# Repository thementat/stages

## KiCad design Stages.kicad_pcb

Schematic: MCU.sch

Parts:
C3, C4: 20p; C_0805_2012Metric
C9: 22u; C_1206_3216Metric
C11, C13, C14, C24: 100n; C_0805_2012Metric
C12, C26: 1u; C_0805_2012Metric
IC5: STM32F373RBTx; LQFP-64_10x10mm_P0.5mm
JP3, JP4: Conn_01x03; PinHeader_1x03_P2.54mm_Vertical
JP6: Conn_01x04; PinHeader_1x04_P2.54mm_Vertical
Q1: 8MHz; Crystal_SMD_Abracon_ABMM2-4Pin_6.0x3.6mm_HandSoldering
R5, R7, R8, R9, R10, R11: 100; R_0805_2012Metric
R12: 10k; R_0805_2012Metric

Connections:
+3V3: C9.1, C11.1, C14.1, IC5.1 (VBAT), IC5.19 (VDD), IC5.64 (VDD), R12.2; also elsewhere on the board
+3V3_A: C12.1, C13.1, C24.1, C26.1, IC5.13 (VDDA), IC5.17 (VREF+), IC5.32 (VDDSD), IC5.33 (VREFSD+); also elsewhere on the board
ADC_CV_1: IC5.34 (PB14); also elsewhere on the board
ADC_CV_2: IC5.35 (PB15); also elsewhere on the board
ADC_CV_3: IC5.29 (PE8); also elsewhere on the board
ADC_CV_4: IC5.30 (PE9); also elsewhere on the board
ADC_CV_5: IC5.27 (PB1); also elsewhere on the board
ADC_CV_6: IC5.26 (PB0); also elsewhere on the board
ADC_SHAPE: IC5.22 (PA6); also elsewhere on the board
ADC_TIME_LEVEL: IC5.23 (PA7); also elsewhere on the board
DAC_MOSI: IC5.53 (PC12); also elsewhere on the board
DAC_SCK: IC5.51 (PC10); also elsewhere on the board
DAC_SS: IC5.50 (PA15); also elsewhere on the board
GATE_1: IC5.44 (PA11); also elsewhere on the board
GATE_2: IC5.43 (PA10); also elsewhere on the board
GATE_3: IC5.42 (PA9); also elsewhere on the board
GATE_4: IC5.41 (PA8); also elsewhere on the board
GATE_5: IC5.39 (PC8); also elsewhere on the board
GATE_6: IC5.38 (PC7); also elsewhere on the board
LEDS_SCK: IC5.58 (PB6); also elsewhere on the board
LEDS_SIN: IC5.57 (PB5); also elsewhere on the board
LEDS_SS: IC5.59 (PB7); also elsewhere on the board
LEFT_RX: IC5.62 (PB9), R7.1
LEFT_TX: IC5.61 (PB8), R5.1
NORMALIZATION_PROBE: IC5.40 (PC9); also elsewhere on the board
unnamed: C3.2, Q1.1, R9.1
unnamed: C4.2, Q1.3, R8.1
unnamed: IC5.5 (PF0), R9.2
unnamed: IC5.6 (PF1), R8.2
unnamed: JP3.2, R5.2
unnamed: JP3.3, R7.2
unnamed: JP4.2, R10.2
unnamed: JP4.3, R11.2
POTS_ADDR_A: IC5.21 (PA5); also elsewhere on the board
POTS_ADDR_B: IC5.20 (PA4); also elsewhere on the board
POTS_ADDR_C: IC5.18 (PA3); also elsewhere on the board
RESET: IC5.7 (NRST), JP6.4, R12.1
RIGHT_RX: IC5.25 (PC5), R10.1
RIGHT_TX: IC5.24 (PC4), R11.1
STAGE_LED_1: IC5.45 (PA12); also elsewhere on the board
STAGE_LED_2: IC5.2 (PC13); also elsewhere on the board
STAGE_LED_3: IC5.3 (PC14); also elsewhere on the board
STAGE_LED_4: IC5.4 (PC15); also elsewhere on the board
STAGE_LED_5: IC5.16 (PA2); also elsewhere on the board
STAGE_LED_6: IC5.28 (PB2); also elsewhere on the board
SWCLK: IC5.49 (PA14), JP6.3
SWDIO: IC5.46 (PA13), JP6.2
SW_MODE_1: IC5.8 (PC0); also elsewhere on the board
SW_MODE_2: IC5.9 (PC1); also elsewhere on the board
SW_MODE_3: IC5.10 (PC2); also elsewhere on the board
SW_MODE_4: IC5.11 (PC3); also elsewhere on the board
SW_MODE_5: IC5.14 (PA0); also elsewhere on the board
SW_MODE_6: IC5.15 (PA1); also elsewhere on the board

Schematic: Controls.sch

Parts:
C5, C7, C8, C16: 100n; C_0805_2012Metric
C6: 22u; C_1206_3216Metric
IC1: TLC59281; TSSOP-24_4.4x7.8mm_P0.65mm
IC3, IC6: 4051; TSSOP-16_4.4x5mm_P0.65mm
L2: Ferrite_Bead_Small; R_0805_2012Metric
LED7, LED8, LED9, LED10, LED11, LED12: LED_Dual_CAC; LED_3.0mm Bi-Color Common Anode
MH1, MH2, MH3: MountingHole; MountingHole_3.2mm_M3
R1, R2, R3, R4, R17, R18: 15k; R_0805_2012Metric
R6: 10k; R_0805_2012Metric
R78, R79, R80, R81, R82, R83: 20kB; Potentiometer-Bourns PTL20
R84, R85, R86, R87, R88, R89: 10kB; Potentiometer_SongHuei9mm-1_Single_Vertical
SW1, SW2, SW3, SW4, SW5, SW6: SW_Push_4pin; Push E-Switch 6mm

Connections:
+3V3: L2.1, LED7.2, LED8.2, LED9.2, LED10.2, LED11.2, LED12.2; also elsewhere on the board
+3V3_A: C5.1, C7.1, C16.1, IC3.16, IC6.16, R78.3, R79.3, R80.3, R81.3, R82.3, R83.3, R84.1, R85.1, R86.1, R87.1, R88.1, R89.1; also elsewhere on the board
ADC_SHAPE: IC3.3; also elsewhere on the board
ADC_TIME_LEVEL: IC6.3; also elsewhere on the board
LEDS_SCK: IC1.3; also elsewhere on the board
LEDS_SIN: IC1.2; also elsewhere on the board
LEDS_SS: IC1.4; also elsewhere on the board
unnamed: C6.1, C8.1, IC1.24, L2.2
unnamed: IC1.7, LED9.3
unnamed: IC1.8, LED9.1
unnamed: IC1.9, LED7.1
unnamed: IC1.10, LED7.3
unnamed: IC1.11, LED8.1
unnamed: IC1.12, LED8.3
unnamed: IC1.13, LED10.1
unnamed: IC1.14, LED10.3
unnamed: IC1.15, LED11.3
unnamed: IC1.16, LED11.1
unnamed: IC1.17, LED12.3
unnamed: IC1.18, LED12.1
unnamed: IC1.23, R6.1
unnamed: IC3.1, R86.2
unnamed: IC3.2, R85.2
unnamed: IC3.4, R89.2
unnamed: IC3.5, R84.2
unnamed: IC3.14, R87.2
unnamed: IC3.15, R88.2
unnamed: IC6.1, R78.2
unnamed: IC6.2, R83.2
unnamed: IC6.12, R82.2
unnamed: IC6.13, R81.2
unnamed: IC6.14, R80.2
unnamed: IC6.15, R79.2
unnamed: R1.1, R80.5
unnamed: R2.1, R81.5
unnamed: R3.1, R79.5
unnamed: R4.1, R82.5
unnamed: R17.1, R78.5
unnamed: R18.1, R83.5
POTS_ADDR_A: IC3.9, IC6.11; also elsewhere on the board
POTS_ADDR_B: IC3.10, IC6.10; also elsewhere on the board
POTS_ADDR_C: IC3.11, IC6.9; also elsewhere on the board
STAGE_LED_1: R17.2; also elsewhere on the board
STAGE_LED_2: R3.2; also elsewhere on the board
STAGE_LED_3: R1.2; also elsewhere on the board
STAGE_LED_4: R2.2; also elsewhere on the board
STAGE_LED_5: R4.2; also elsewhere on the board
STAGE_LED_6: R18.2; also elsewhere on the board
SW_MODE_1: SW1.3, SW1.4; also elsewhere on the board
SW_MODE_2: SW2.3, SW2.4; also elsewhere on the board
SW_MODE_3: SW3.3, SW3.4; also elsewhere on the board
SW_MODE_4: SW4.3, SW4.4; also elsewhere on the board
SW_MODE_5: SW5.3, SW5.4; also elsewhere on the board
SW_MODE_6: SW6.3, SW6.4; also elsewhere on the board

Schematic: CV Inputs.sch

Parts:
C27, C29, C31, C32, C35: 2.2n; C_0805_2012Metric
C28: 470p; C_0805_2012Metric
C30, C33, C34: 100n; C_0805_2012Metric
C36, C37, C38, C39, C40, C42: ESD; C_0805_2012Metric
IC8, IC9, IC10: MCP6002; SOIC-8_3.9x4.9mm_P1.27mm
J13, J14, J15, J16, J17, J18: -81V to 8.1V; WQP-PJ301M-12_JACK
R13, R14, R15, R16, R19, R20: 20k; R_0805_2012Metric
R21, R22, R23, R24, R26, R29: 30k; R_0805_2012Metric
R25, R27, R28, R30, R31, R32: 100k; R_0805_2012Metric

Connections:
+3V3_A: C30.1, C33.1, C34.1, IC8.8 (V+), IC9.8 (V+), IC10.8 (V+); also elsewhere on the board
ADC_CV_1: C35.1, IC10.7, R16.1; also elsewhere on the board
ADC_CV_2: C32.1, IC10.1, R14.1; also elsewhere on the board
ADC_CV_3: C31.1, IC9.7, R13.1; also elsewhere on the board
ADC_CV_4: C29.1, IC9.1, R15.1; also elsewhere on the board
ADC_CV_5: C27.1, IC8.7, R19.1; also elsewhere on the board
ADC_CV_6: C28.1, IC8.1, R20.1; also elsewhere on the board
AREF_-2.5: R21.2, R22.2, R23.2, R24.2, R26.2, R29.2; also elsewhere on the board
unnamed: C27.2, IC8.6 (-), R19.2, R24.1, R31.1
unnamed: C28.2, IC8.2 (-), R20.2, R23.1, R32.1
unnamed: C29.2, IC9.2 (-), R15.2, R22.1, R25.1
unnamed: C31.2, IC9.6 (-), R13.2, R26.1, R27.1
unnamed: C32.2, IC10.2 (-), R14.2, R21.1, R28.1
unnamed: C35.2, IC10.6 (-), R16.2, R29.1, R30.1
unnamed: C36.1, J17.P$1, R31.2
unnamed: C37.1, J15.P$1, R27.2
unnamed: C38.1, J13.P$1, R30.2
unnamed: C39.1, J14.P$1, R28.2
unnamed: C40.1, J16.P$1, R25.2
unnamed: C42.1, J18.P$1, R32.2

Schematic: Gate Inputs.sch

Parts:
D3, D4, D5, D6, D7, D8: 1N4148; D_SOD-123
D9: BAT54S; D_SOT-23_NKA
J7, J8, J9, J10, J11, J12: WQP-PJ301M-12_JACK
Q2, Q3, Q4, Q5, Q6, Q7: MMBT3904; SOT-23
R60, R61, R62, R63, R64, R65: 10k; R_0603_1608Metric_Pad1.05x0.95mm_HandSolder
R66, R67, R68, R69, R70, R71, R72, R73, R74, R75, R76, R77: 100k; R_0603_1608Metric_Pad1.05x0.95mm_HandSolder

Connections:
+3V3: D9.2; also elsewhere on the board
GATE_1: Q7.3 (C); also elsewhere on the board
GATE_2: Q3.3 (C); also elsewhere on the board
GATE_3: Q6.3 (C); also elsewhere on the board
GATE_4: Q4.3 (C); also elsewhere on the board
GATE_5: Q5.3 (C); also elsewhere on the board
GATE_6: Q2.3 (C); also elsewhere on the board
NORMALIZATION_PROBE: D9.3, R60.2, R61.2, R62.2, R63.2, R64.2, R65.2; also elsewhere on the board
unnamed: D3.1, Q7.1 (B), R66.2, R69.2
unnamed: D4.1, Q5.1 (B), R67.2, R70.2
unnamed: D5.1, Q6.1 (B), R68.2, R71.2
unnamed: D6.1, Q2.1 (B), R74.2, R75.2
unnamed: D7.1, Q3.1 (B), R73.2, R77.2
unnamed: D8.1, Q4.1 (B), R72.2, R76.2
unnamed: J7.P$1, R66.1
unnamed: J7.P$2, R65.1
unnamed: J8.P$1, R77.1
unnamed: J8.P$2, R62.1
unnamed: J9.P$1, R68.1
unnamed: J9.P$2, R63.1
unnamed: J10.P$1, R76.1
unnamed: J10.P$2, R61.1
unnamed: J11.P$1, R67.1
unnamed: J11.P$2, R64.1
unnamed: J12.P$1, R75.1
unnamed: J12.P$2, R60.1

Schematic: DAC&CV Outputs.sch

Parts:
C18, C43: 1u; C_0805_2012Metric
C22: 22u; C_1206_3216Metric
C44, C45, C46, C47, C48, C49: 100p; C_0805_2012Metric
C50, C51, C52, C53, C54, C55: 100n; C_0805_2012Metric
IC4: DAC8168; TSSOP-14_4.4x5mm_P0.65mm
IC12, IC13, IC14: TL074; TSSOP-14_4.4x5mm_P0.65mm
J1, J2, J3, J4, J5, J6: -8.1V to 8.1V; WQP-PJ301M-12_JACK
LED1, LED2, LED3, LED4, LED5, LED6: WP937EGW; LED_D3.0mm
R34, R35, R36, R37, R38, R39, R54, R55, R56, R57, R58, R59: 1k; R_0805_2012Metric
R40, R41, R42, R43, R44, R45, R46: 130k; R_0805_2012Metric
R47, R49, R50, R51, R52, R53: 20k; R_0805_2012Metric
R48: 100k; R_0805_2012Metric

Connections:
+3V3_A: C18.1, C22.1, IC4.2; also elsewhere on the board
AREF_2.5: IC4.7, R40.1
DAC_1: IC4.10, R52.2
DAC_2: IC4.11, R51.2
DAC_3: IC4.6, R53.2
DAC_4: IC4.4, R49.2
DAC_5: IC4.3, R50.2
DAC_6: IC4.5, R47.2
DAC_MOSI: IC4.13; also elsewhere on the board
DAC_SCK: IC4.14; also elsewhere on the board
DAC_SS: IC4.1; also elsewhere on the board
unnamed: C44.1, IC12.1, IC12.5 (+), R35.2
unnamed: C44.2, IC12.2 (-), R41.2, R47.1
unnamed: C45.1, IC12.10 (+), IC12.14, R34.2
unnamed: C45.2, IC12.13 (-), R42.2, R50.1
unnamed: C46.1, IC13.1, IC13.5 (+), R36.2
unnamed: C46.2, IC13.2 (-), R43.2, R49.1
unnamed: C47.1, IC13.10 (+), IC13.14, R38.2
unnamed: C47.2, IC13.13 (-), R44.2, R53.1
unnamed: C48.1, IC14.1, IC14.5 (+), R37.2
unnamed: C48.2, IC14.2 (-), R45.2, R51.1
unnamed: C49.1, IC14.10 (+), IC14.14, R39.2
unnamed: C49.2, IC14.13 (-), R46.2, R52.1
unnamed: IC12.6 (-), LED4.2, R54.1
unnamed: IC12.7, LED4.1
unnamed: IC12.8, LED6.1
unnamed: IC12.9 (-), LED6.2, R55.1
unnamed: IC13.6 (-), LED3.2, R56.1
unnamed: IC13.7, LED3.1
unnamed: IC13.8, LED2.1
unnamed: IC13.9 (-), LED2.2, R57.1
unnamed: IC14.6 (-), LED5.2, R58.1
unnamed: IC14.7, LED5.1
unnamed: IC14.8, LED1.1
unnamed: IC14.9 (-), LED1.2, R59.1
unnamed: J1.P$1, R39.1, R46.1
unnamed: J2.P$1, R37.1, R45.1
unnamed: J3.P$1, R38.1, R44.1
unnamed: J4.P$1, R36.1, R43.1
unnamed: J5.P$1, R34.1, R42.1
unnamed: J6.P$1, R35.1, R41.1
VCC: C50.1, C52.1, C54.1, IC12.4 (V+), IC13.4 (V+), IC14.4 (V+); also elsewhere on the board
VEE: C51.2, C53.2, C55.2, IC12.11 (V-), IC13.11 (V-), IC14.11 (V-); also elsewhere on the board
VREF_BIAS: C43.1, IC12.3 (+), IC12.12 (+), IC13.3 (+), IC13.12 (+), IC14.3 (+), IC14.12 (+), R40.2, R48.1

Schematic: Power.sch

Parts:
C1, C2, C10, C19, C20, C21, C23, C25: 22u; C_1206_3216Metric
C15: 100n; C_0805_2012Metric
C17: 22u; C_0805_2012Metric
C41: 1u; C_0805_2012Metric
D1, D2: D; D_SOD-123
IC2: R-78E3.3-0.5; Converter_DCDC_RECOM_ROF-78E-0.5_SMD_HandSoldering
IC7: LD2981ABU33; SOT-89-3_Handsoldering
IC11: LM4040DBZ-2.5; SOT-23
JP5: M05X2SMD; PinHeader_2x05_P2.54mm_Vertical_SMD
L1, L5: Ferrite_Bead; R_0805_2012Metric
L3: 33u; L_0805_2012Metric
L4: Ferrite_Bead_Small; R_0805_2012Metric
MH4: MountingHole_Pad; PinHeader_1x01_P1.00mm_Vertical
R33: 10k; R_0805_2012Metric

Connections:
+3V3: C10.1, C15.1, IC2.3 (OUT); also elsewhere on the board
+3V3_A: C20.1, IC7.1; also elsewhere on the board
AREF_-2.5: C41.1, IC11.2 (A), R33.1; also elsewhere on the board
unnamed: C17.1, D2.1, L3.1, L4.2, L5.2
unnamed: C19.1, IC2.1 (IN), L3.2
unnamed: C23.1, IC7.3, L4.1
unnamed: D1.1, JP5.9, JP5.10
unnamed: D1.2, L1.2
unnamed: D2.2, JP5.1, JP5.2
VCC: C21.1, C25.1, L5.1; also elsewhere on the board
VEE: C1.2, C2.2, L1.1, R33.2; also elsewhere on the board

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
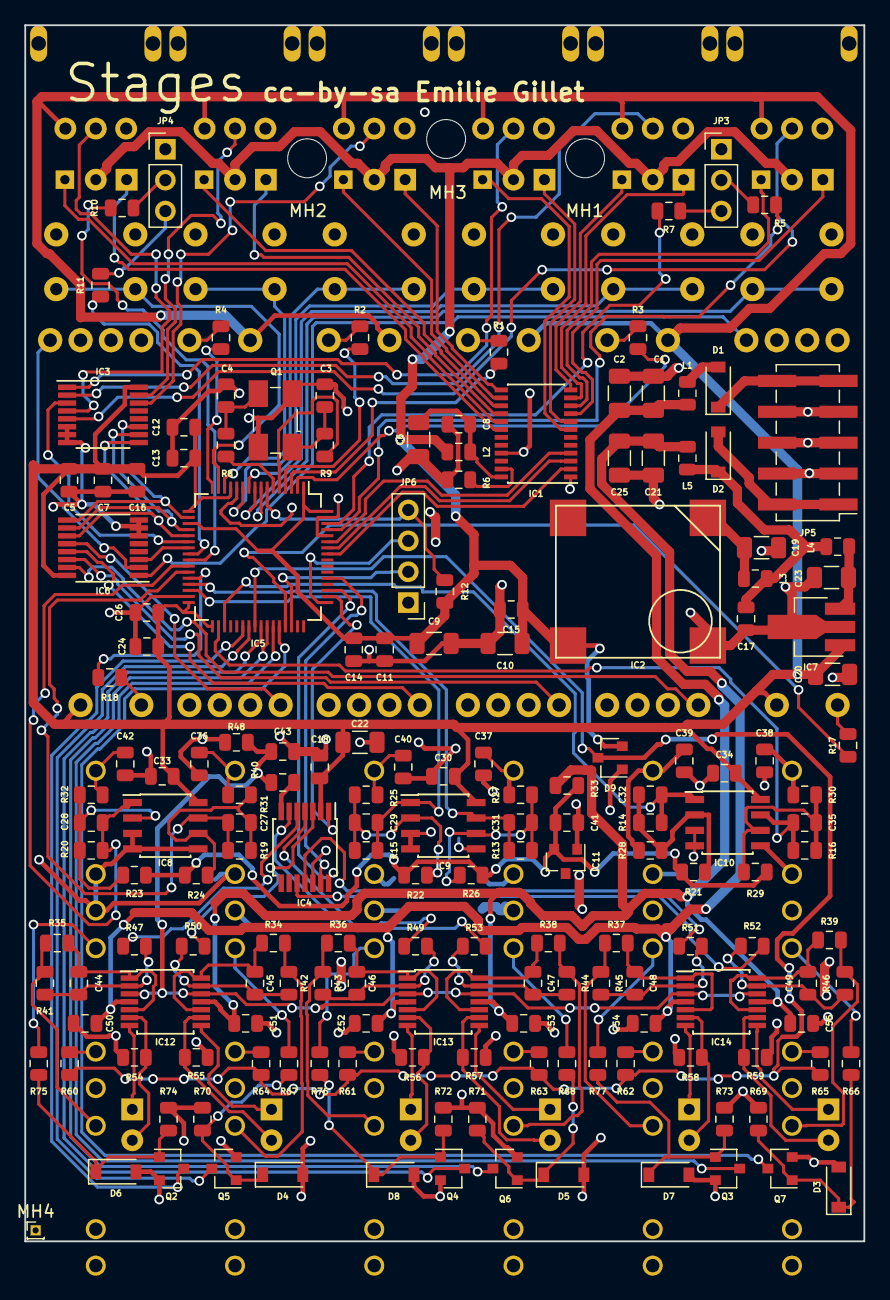
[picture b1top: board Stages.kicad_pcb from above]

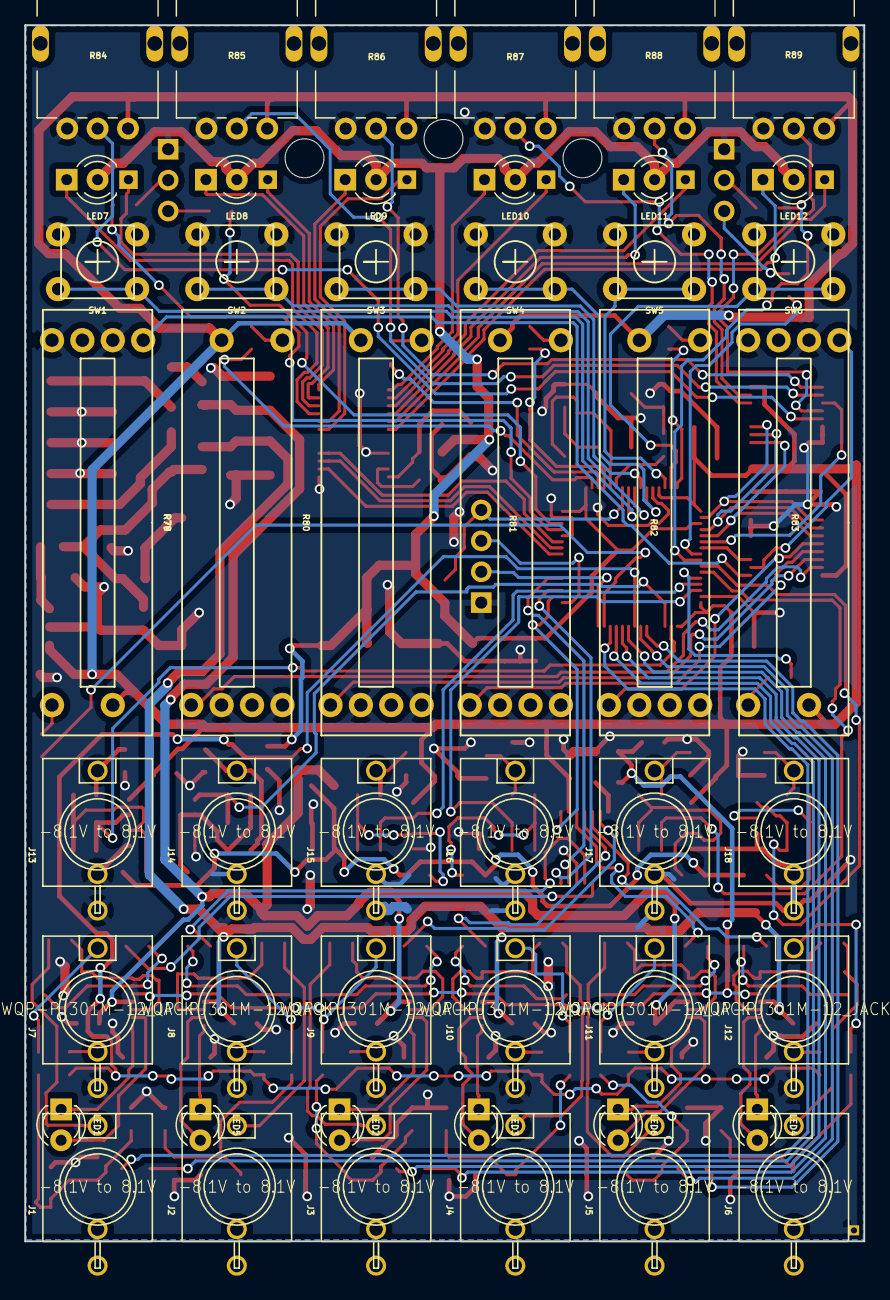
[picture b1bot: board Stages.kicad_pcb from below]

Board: 2 copper layers, 69.0 x 100.0 mm, 223 parts (48 on the bottom side), 163 nets.

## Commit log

2018-12-06 Initial Add
2018-12-07 Refinements
2018-12-11 Rough Placement Completed
    Completed the rough placement of the components on the pcb
2018-12-13 Progress on routing tracks
    Most of the power tracks are routed
2018-12-18 Re-oriented several components
2018-12-19 Re-orientation
    Fixed some bad op-amp orientations
2018-12-23 Added Mounting Holes
2018-12-24 Routing Complete
    time to tidy up connections
2018-12-27 DRC Complete
2018-12-27 Removed to plane and re-routed
2018-12-27 Tidy up Ground outes
2019-01-01 Fixed Component pinouts
2019-01-02 Submitted Design
2019-02-18 Initial Conversion
2019-03-17 BOM update

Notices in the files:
Stages.kicad_pcb:
cc-by-sa Emilie Gillet
